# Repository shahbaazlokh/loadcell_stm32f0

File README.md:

# loadcell_stm32f0
loadcell with STM32f0 and oled display with pcb design and application code

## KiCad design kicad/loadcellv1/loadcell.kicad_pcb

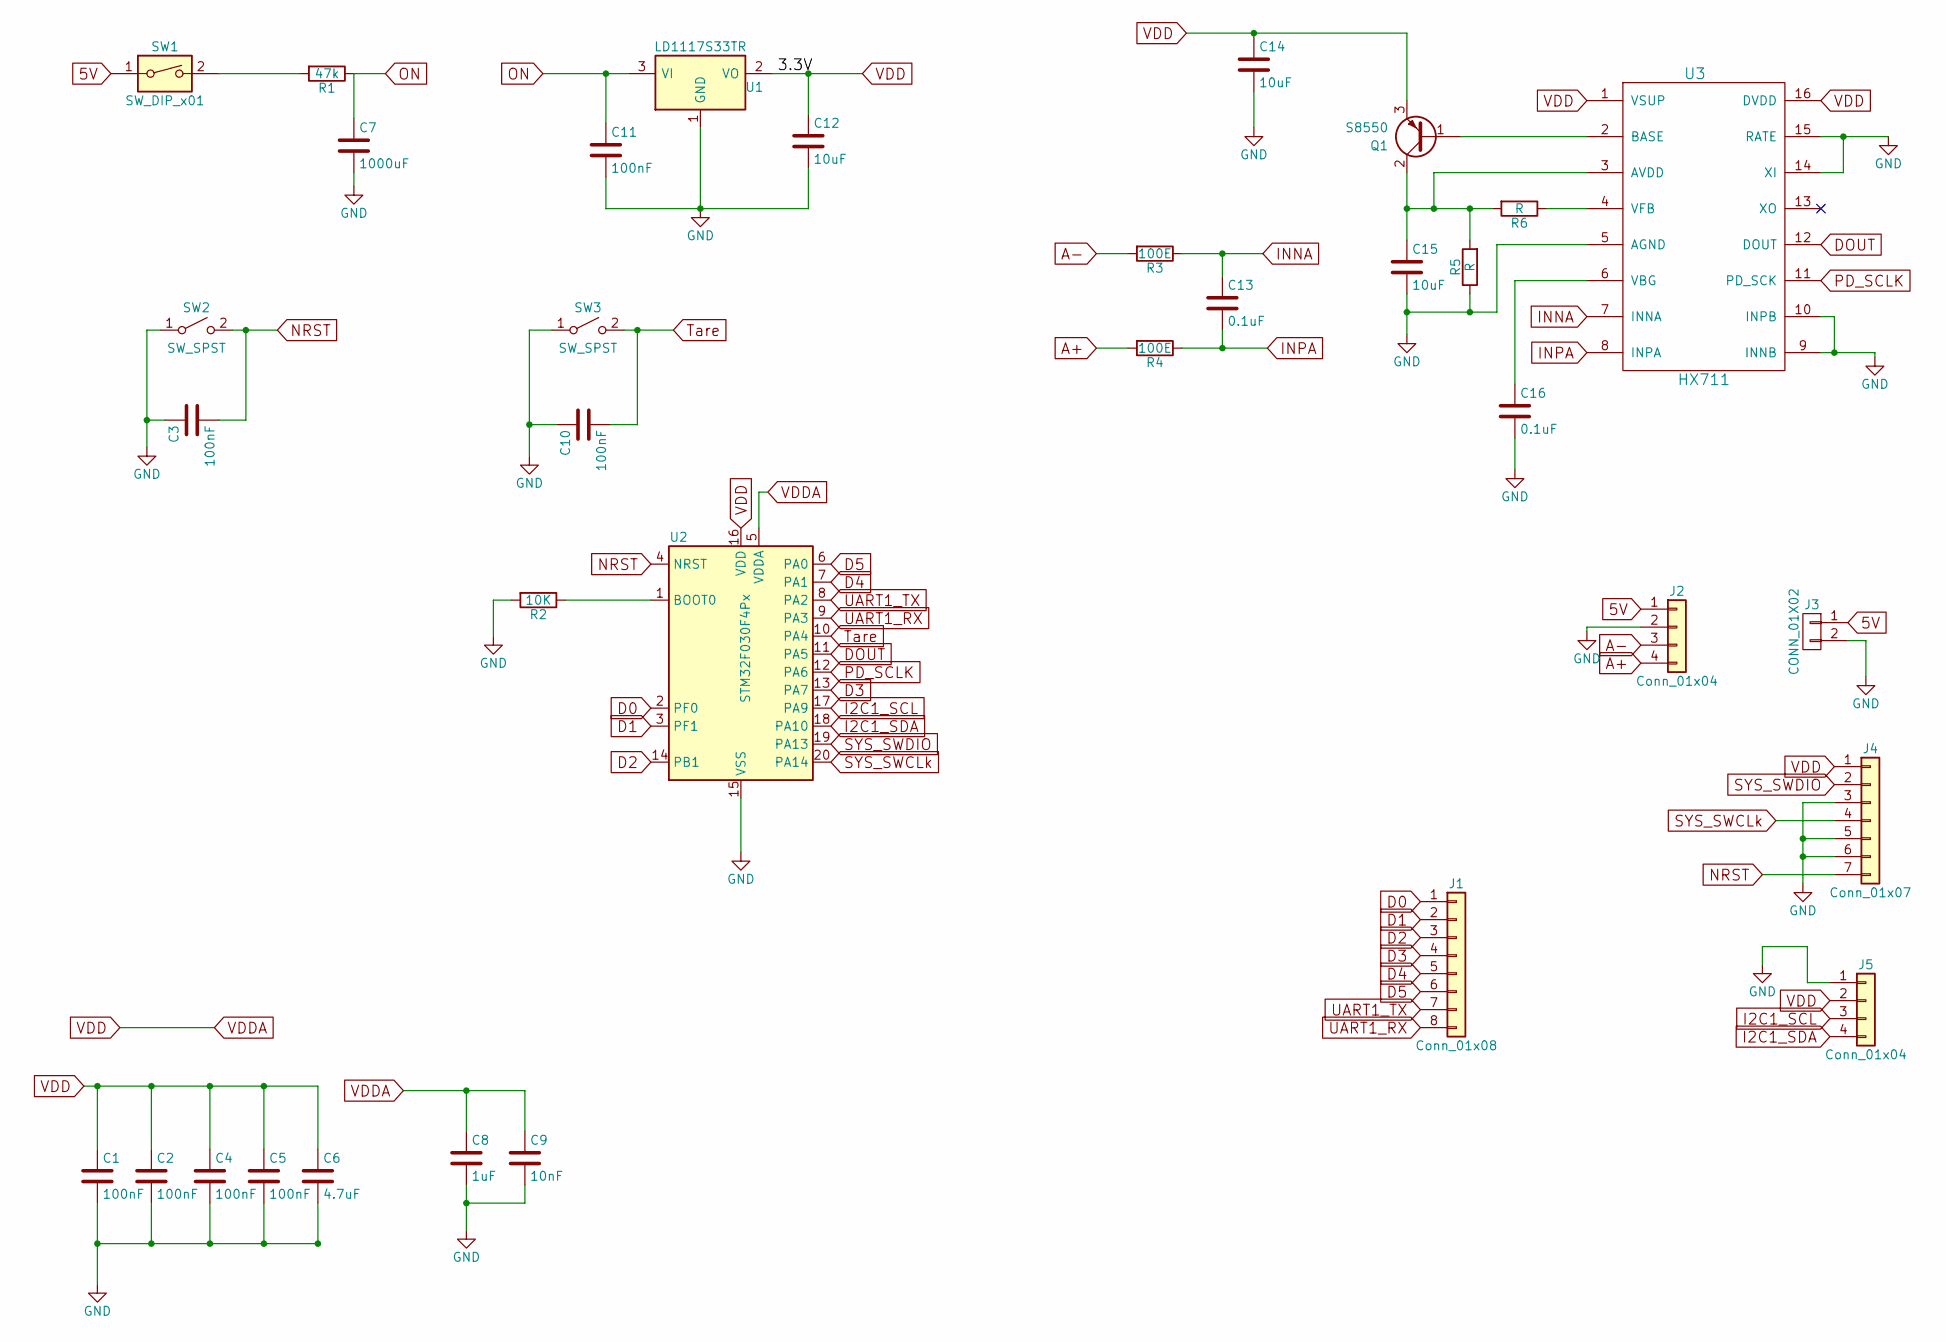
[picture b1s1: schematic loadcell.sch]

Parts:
C1, C2, C3, C4, C5, C10, C11: 100nF; C_1206_HandSoldering
C6: 4.7uF; C_1206_HandSoldering
C7: 1000uF; C_1206_HandSoldering
C8: 1uF; C_1206_HandSoldering
C9: 10nF; C_1206_HandSoldering
C12, C14, C15: 10uF; C_1206_HandSoldering
C13, C16: 0.1uF; C_1206_HandSoldering
J1: Conn_01x08; Pin_Header_Straight_1x08_Pitch2.54mm
J2, J5: Conn_01x04; Pin_Header_Straight_1x04_Pitch2.54mm
J3: CONN_01X02; Pin_Header_Straight_1x02_Pitch2.54mm
J4: Conn_01x07; Pin_Header_Straight_1x07_Pitch2.54mm
Q1: S8550; SOT-23
R1: 47k; R_1206_HandSoldering
R2: 10K; R_1206_HandSoldering
R3, R4: 100E; R_1206_HandSoldering
R5, R6: R; R_1206_HandSoldering
SW1: SW_DIP_x01; SW_DIP_x1_W5.08mm_Slide_Copal_CHS-A
SW2, SW3: SW_SPST; SW_SPST_B3U-1000P
U1: LD1117S33TR; SOT-223
U2: STM32F030F4Px; SSOP-20_4.4x6.5mm_Pitch0.65mm
U3: HX711; SOP-16_4.4x10.4mm_Pitch1.27mm

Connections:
5V: J2.1, J3.1, SW1.1
A+: J2.4, R4.2
A-: J2.3, R3.2
D0: J1.1, U2.2 (PF0)
D1: J1.2, U2.3 (PF1)
D2: J1.3, U2.14 (PB1)
D3: J1.4, U2.13 (PA7)
D4: J1.5, U2.7 (PA1)
D5: J1.6, U2.6 (PA0)
DOUT: U2.11 (PA5), U3.12 (DOUT)
GND: C1.2, C2.2, C3.1, C4.2, C5.2, C6.2, C7.2, C8.2, C9.2, C10.1, C11.2, C12.2, C14.2, C15.2, C16.2, J2.2, J3.2, J4.3, J4.5, J4.6, J5.1, R2.2, R5.1, SW2.1 (A), SW3.1 (A), U1.1 (GND), U2.15 (VSS), U3.5 (AGND), U3.9 (INNB), U3.10 (INPB), U3.14 (XI), U3.15 (RATE)
I2C1_SCL: J5.3, U2.17 (PA9)
I2C1_SDA: J5.4, U2.18 (PA10)
INNA: C13.1, R3.1, U3.7 (INNA)
INPA: C13.2, R4.1, U3.8 (INPA)
NRST: C3.2, J4.7, SW2.2 (B), U2.4 (NRST)
unnamed: C15.1, Q1.2 (C), R5.2, R6.2, U3.3 (AVDD)
unnamed: C16.1, U3.6 (VBG)
unnamed: Q1.1 (B), U3.2 (BASE)
unnamed: R1.2, SW1.2
unnamed: R2.1, U2.1 (BOOT0)
unnamed: R6.1, U3.4 (VFB)
ON: C7.1, C11.1, R1.1, U1.3 (VI)
PD_SCLK: U2.12 (PA6), U3.11 (PD_SCK)
SYS_SWCLk: J4.4, U2.20 (PA14)
SYS_SWDIO: J4.2, U2.19 (PA13)
Tare: C10.2, SW3.2 (B), U2.10 (PA4)
UART1_RX: J1.8, U2.9 (PA3)
UART1_TX: J1.7, U2.8 (PA2)
VDD: C1.1, C2.1, C4.1, C5.1, C6.1, C8.1, C9.1, C12.1, C14.1, J4.1, J5.2, Q1.3 (E), U1.2 (VO), U2.5 (VDDA), U2.16 (VDD), U3.1 (VSUP), U3.16 (DVDD)

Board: 2 copper layers, 34 parts (0 on the bottom side), 30 nets, no tracks yet.
